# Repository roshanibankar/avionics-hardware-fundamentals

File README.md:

## Reference: Art of Electronics: Student Manual co-authored by Thomas C. Hayes and Paul Horowitz 

## EMBEDDED CIRCUITS
- Aduio Light Sync [Mosfets, audio amplifiers, arduino UNO] 
- DEPTH
- DINO RUN USING LDR, SERVO MOTORS
- LED VALENTINE DAY HEART WITH TIMER555 SYNCHRONIZATION

---
```
# Guides

- KiCad Guide  
- Altium Guide  
- Fusion360 Guide  
- Matlab Guide
- Arduino Cheatsheet
- Raspberry Pi Cheatsheet
- FPGA Cheatsheet

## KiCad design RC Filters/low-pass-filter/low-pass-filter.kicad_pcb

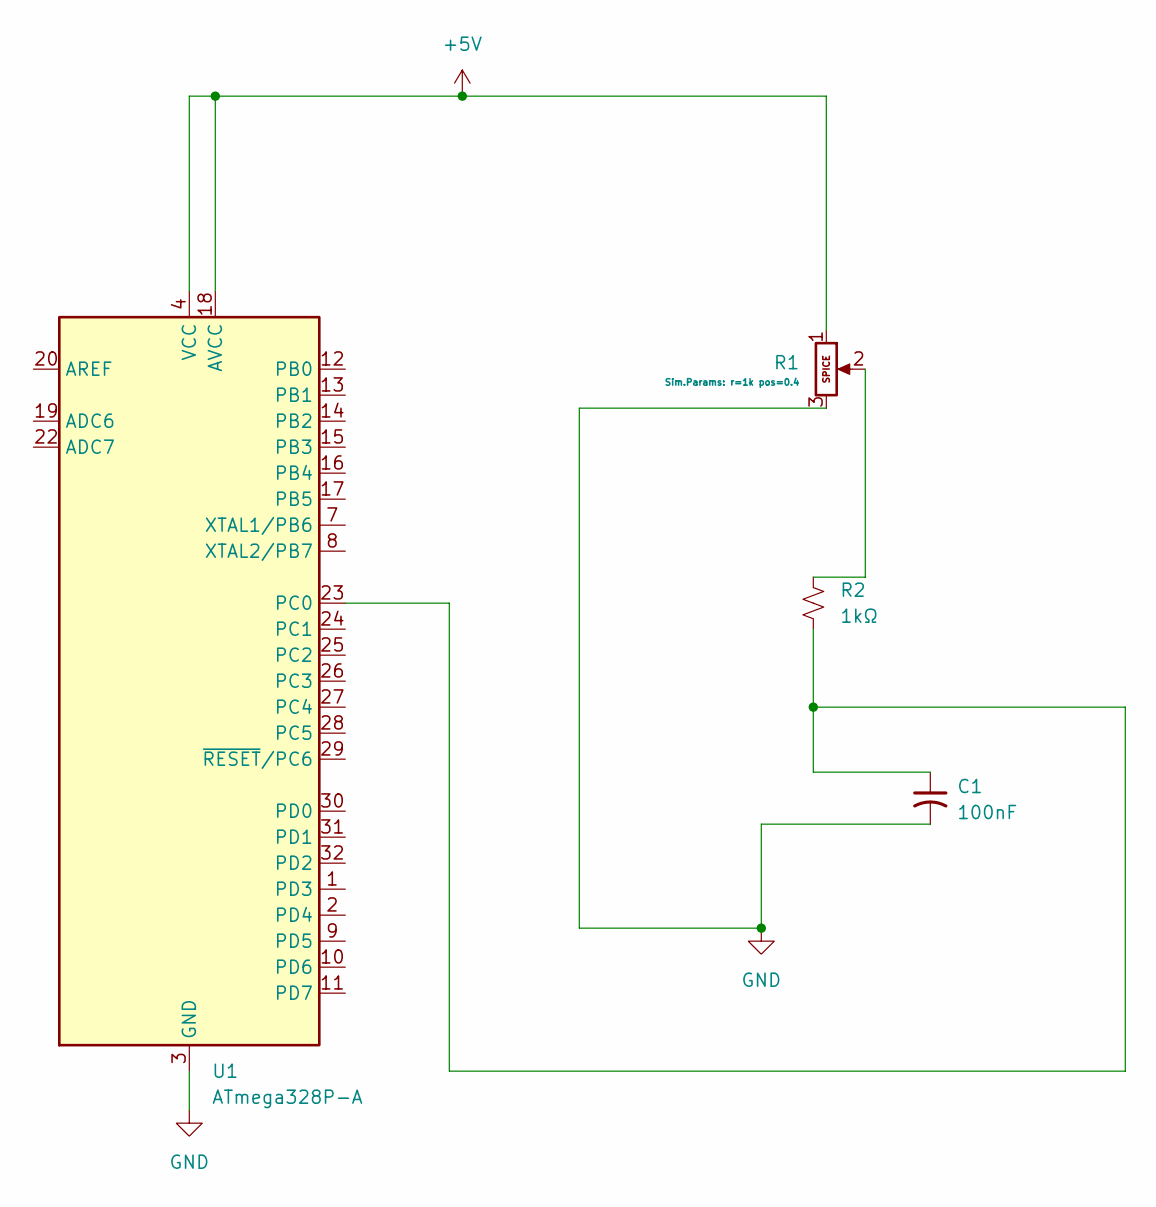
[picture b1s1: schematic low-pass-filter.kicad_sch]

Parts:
C1: 100nF; C_0805_2012Metric
R1: Potentiometer; Potentiometer_Alps_RK09K_Single_Vertical
R2: 1kΩ; R_0805_2012Metric
U1: ATmega328P-A; TQFP-32_7x7mm_P0.8mm

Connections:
+5V: R1.1, U1.4 (VCC), U1.6 (VCC), U1.18 (AVCC)
GND: C1.2, R1.3, U1.3 (GND), U1.5 (GND), U1.21 (GND)
unnamed: R1.2, R2.1
unnamed: C1.1, R2.2, U1.23 (PC0)

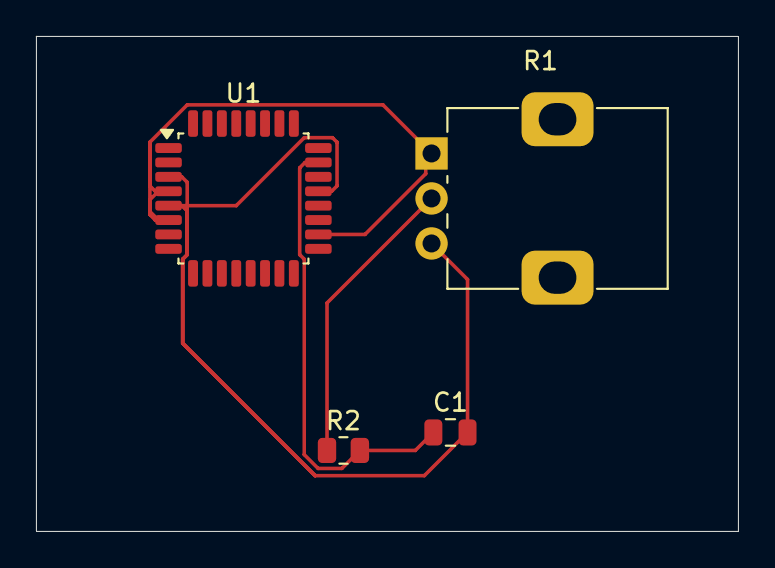
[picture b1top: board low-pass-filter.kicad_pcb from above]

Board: 2 copper layers, 39.0 x 27.5 mm, 4 parts (0 on the bottom side), 4 nets.

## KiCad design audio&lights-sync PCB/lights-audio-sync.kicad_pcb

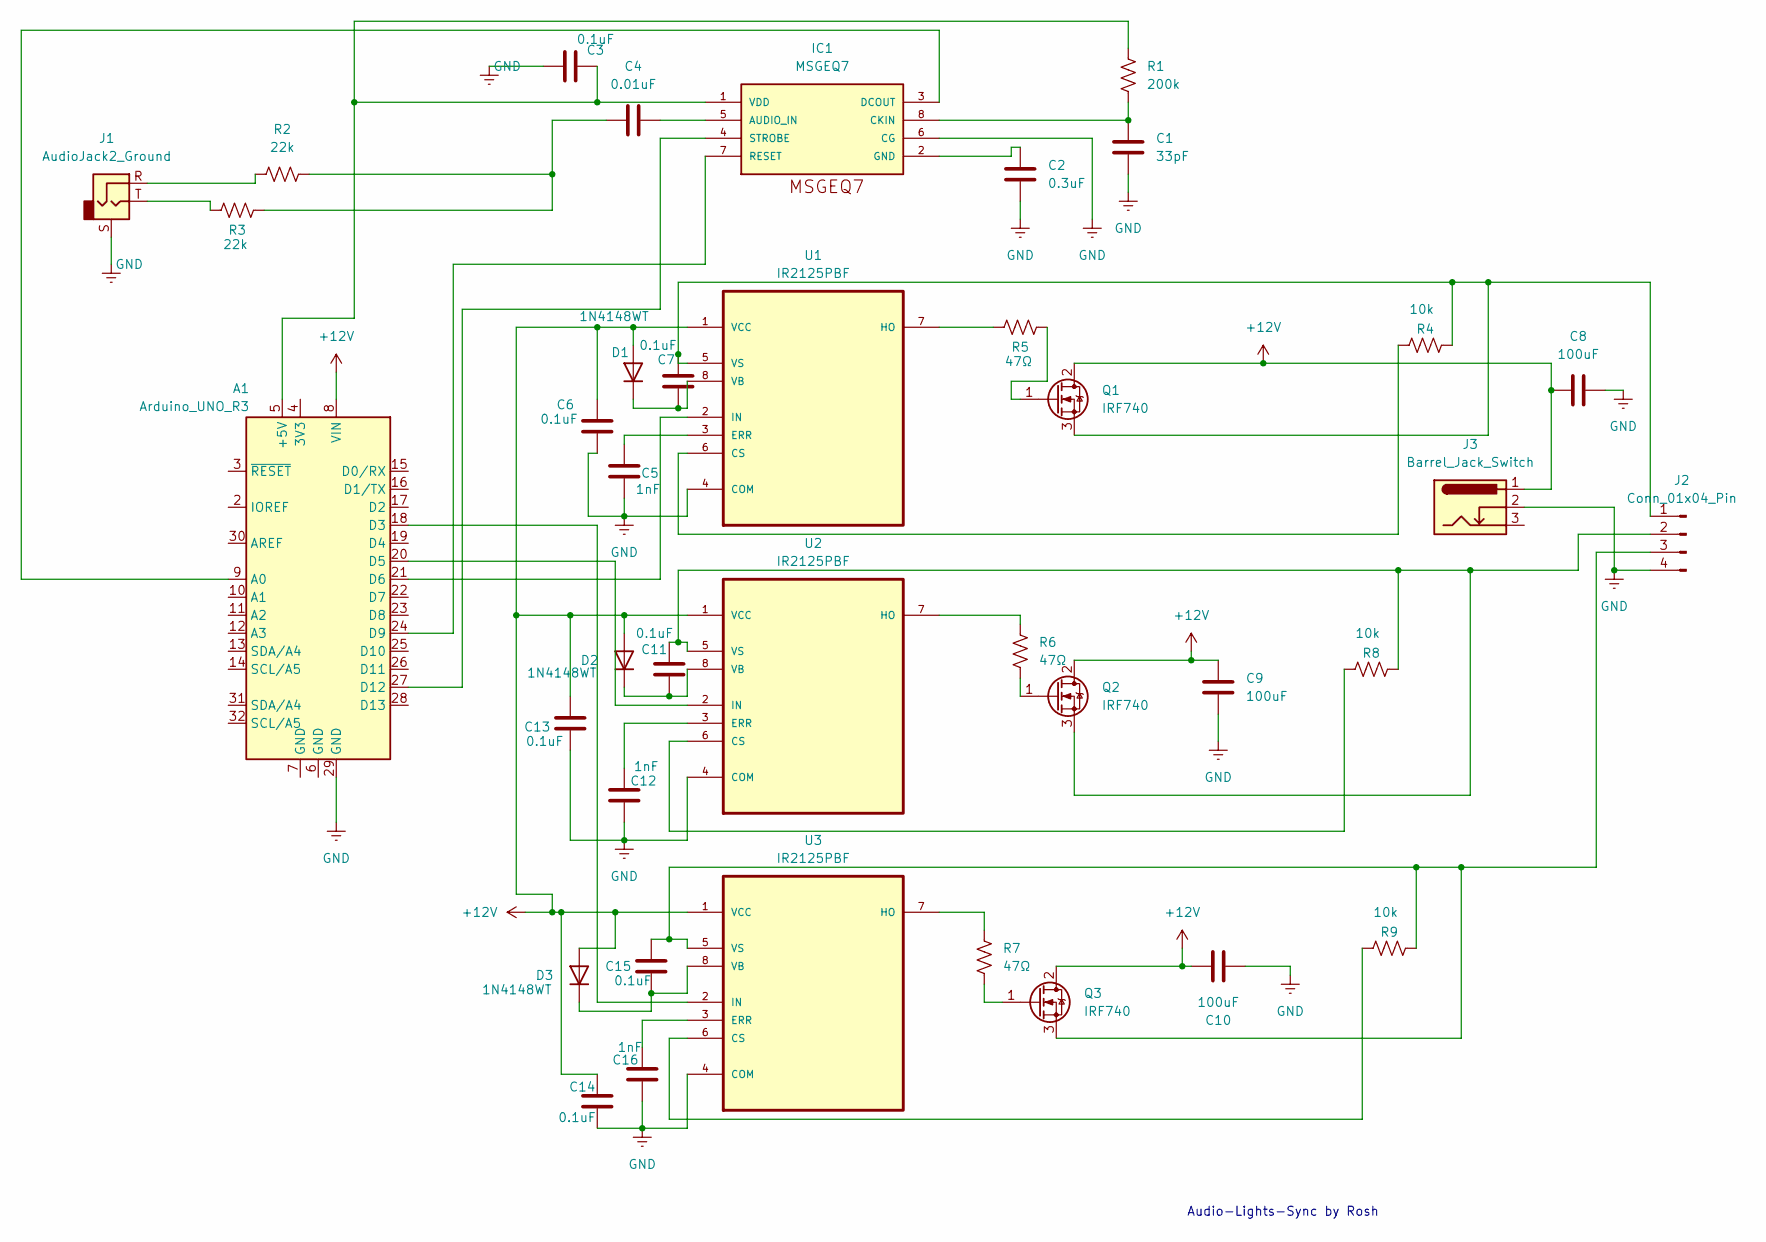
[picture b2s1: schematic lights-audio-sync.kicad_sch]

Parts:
A1: Arduino_UNO_R3
C1: 33pF; C_Disc_D3.0mm_W1.6mm_P2.50mm
C2: 0.3uF; C_Disc_D5.0mm_W2.5mm_P5.00mm
C3, C6, C7, C11, C13, C14, C15: 0.1uF; C_Disc_D5.0mm_W2.5mm_P5.00mm
C4: 0.01uF; C_Disc_D5.0mm_W2.5mm_P5.00mm
C5, C12, C16: 1nF; C_Disc_D3.0mm_W1.6mm_P2.50mm
C8, C9, C10: 100uF; CP_Radial_D6.3mm_P2.50mm
D1, D2, D3: 1N4148WT; D_DO-35_SOD27_P7.62mm_Horizontal
IC1: MSGEQ7; CERDIP-8_W7.62mm_SideBrazed
J1: AudioJack2_Ground; Jack_3.5mm_CUI_SJ1-3523N_Horizontal
J2: Conn_01x04_Pin; PinHeader_1x04_P2.54mm_Vertical
J3: Barrel_Jack_Switch; BarrelJack_Horizontal
Q1, Q2, Q3: IRF740; TO-220-3_Vertical
R1: 200k; R_Axial_DIN0207_L6.3mm_D2.5mm_P7.62mm_Horizontal
R2, R3: 22k; R_Axial_DIN0207_L6.3mm_D2.5mm_P7.62mm_Horizontal
R4, R8, R9: 10k; R_Axial_DIN0207_L6.3mm_D2.5mm_P7.62mm_Horizontal
R5, R6, R7: 47Ω; R_Axial_DIN0207_L6.3mm_D2.5mm_P7.62mm_Horizontal
U1, U2, U3: IR2125PBF; CERDIP-8_W7.62mm_SideBrazed; MPN IR2125PBF; DigiKey_Part_Number IR2125PBF-ND

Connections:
+12V: A1.8 (VIN), C6.1, C8.1, C9.1, C10.2, C13.1, C14.1, D1.2 (A), D2.2 (A), D3.2 (A), J3.1, Q1.2 (D), Q2.2 (D), Q3.2 (D), U1.1 (VCC), U2.1 (VCC), U3.1 (VCC)
GND: A1.29 (GND), C1.2, C2.2, C3.2, C5.2, C6.2, C8.2, C9.2, C10.1, C12.2, C13.2, C14.2, C16.2, IC1.6 (CG), J1.S, J2.4, J3.2, U1.4 (COM), U2.4 (COM), U3.4 (COM)
unnamed: A1.5 (+5V), C3.1, IC1.1 (VDD), R1.1
unnamed: A1.9 (A0), IC1.3 (DCOUT)
unnamed: A1.18 (D3), U3.2 (IN)
unnamed: A1.20 (D5), U2.2 (IN)
unnamed: A1.21 (D6), U1.2 (IN)
unnamed: A1.24 (D9), IC1.7 (RESET)
unnamed: A1.27 (D12), IC1.4 (STROBE)
unnamed: C4.2, R2.1, R3.1
unnamed: C7.2, D1.1 (K), U1.8 (VB)
unnamed: C11.2, D2.1 (K), U2.8 (VB)
unnamed: C15.2, D3.1 (K), U3.8 (VB)
unnamed: C4.1, IC1.5 (AUDIO_IN)
unnamed: C1.1, IC1.8 (CKIN), R1.2
unnamed: C2.1, IC1.2 (GND)
unnamed: J1.R, R2.2
unnamed: J1.T, R3.2
unnamed: C7.1, J2.1, Q1.3 (S), R4.1, U1.5 (VS)
unnamed: C11.1, J2.2, Q2.3 (S), R8.1, U2.5 (VS)
unnamed: C15.1, J2.3, Q3.3 (S), R9.1, U3.5 (VS)
unnamed: Q1.1 (G), R5.1
unnamed: Q2.1 (G), R6.2
unnamed: Q3.1 (G), R7.2
unnamed: R4.2, U1.6 (CS)
unnamed: C5.1, U1.3 (ERR)
unnamed: R5.2, U1.7 (HO)
unnamed: R8.2, U2.6 (CS)
unnamed: C12.1, U2.3 (ERR)
unnamed: R6.1, U2.7 (HO)
unnamed: R9.2, U3.6 (CS)
unnamed: C16.1, U3.3 (ERR)
unnamed: R7.1, U3.7 (HO)

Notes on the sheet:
Audio-Lights-Sync by Rosh

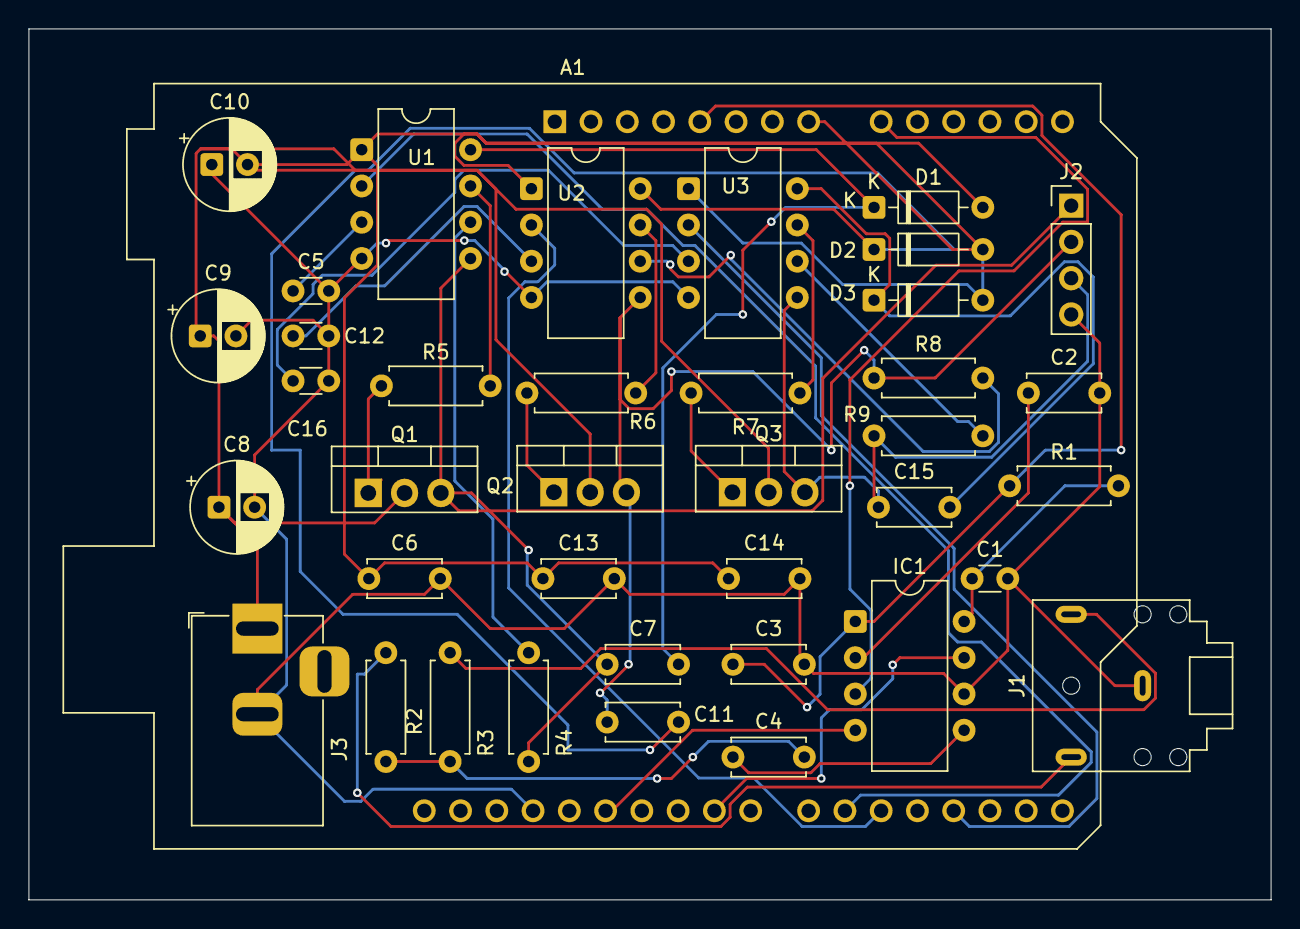
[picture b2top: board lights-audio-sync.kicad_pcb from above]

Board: 2 copper layers, 87.0 x 61.0 mm, 39 parts (0 on the bottom side), 33 nets.

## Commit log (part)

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2026-05-18 damn when am i gonna add these projects??
2026-05-21 Audio-Lights-Sync 2-layer circuit design with code
2026-05-21 2-layer circuit design with code
2026-05-22 2 layer pcb design & code
2026-05-25 2 layer pcb design & code
    Removed 'RC LED Fade Circuit' from the list of filters.
